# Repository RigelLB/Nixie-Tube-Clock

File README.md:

# Nixie-Tube-Clock
This project is based on the Easy Nixie modules made by allexoK. The following link is the Hackaday page for it: https://hackaday.io/project/192446-easynixie

The circuit itself is decently simple, the version built in the photos doesn't include the capacitors but has issues with some power supplies as the lights' striking wattage (turn on wattage) is quite above the specified 10-watt power supply. The chip used for the logic is just a generic esp32. A wire connects P27 to a plate of brass on the top of the clock. As you touch the plate it will turn on for 5 seconds (specified in code).

As a fair warning, the side usb port was put there to program the esp32 without having to take it in and out of its header pins too many times; however, if the switch isn't flipped to the correct side, no power will be supplied. An alternative is to set up the esp32 to be writable OTA.

Some improvements could be made to the electrical design. If you don't prefer having an both LED's be addressible, the posts that hold up the LED's could be used as the conductor to the second plane. 

The later goal in to add OTA code uploading to the esp32, and add a setup page (via webpage) that modifies the wifi SSID and password, time zone, turn on duration, and other features. Another thing will be to move the code to freeRTOS.

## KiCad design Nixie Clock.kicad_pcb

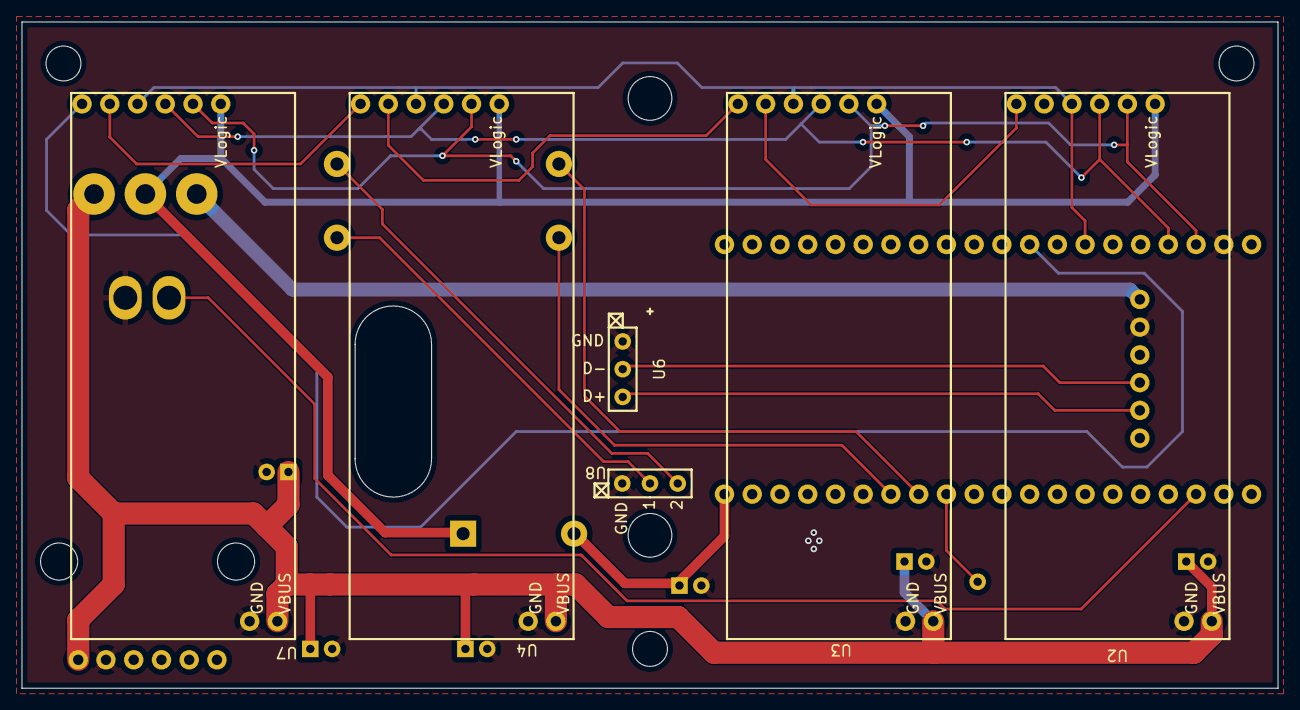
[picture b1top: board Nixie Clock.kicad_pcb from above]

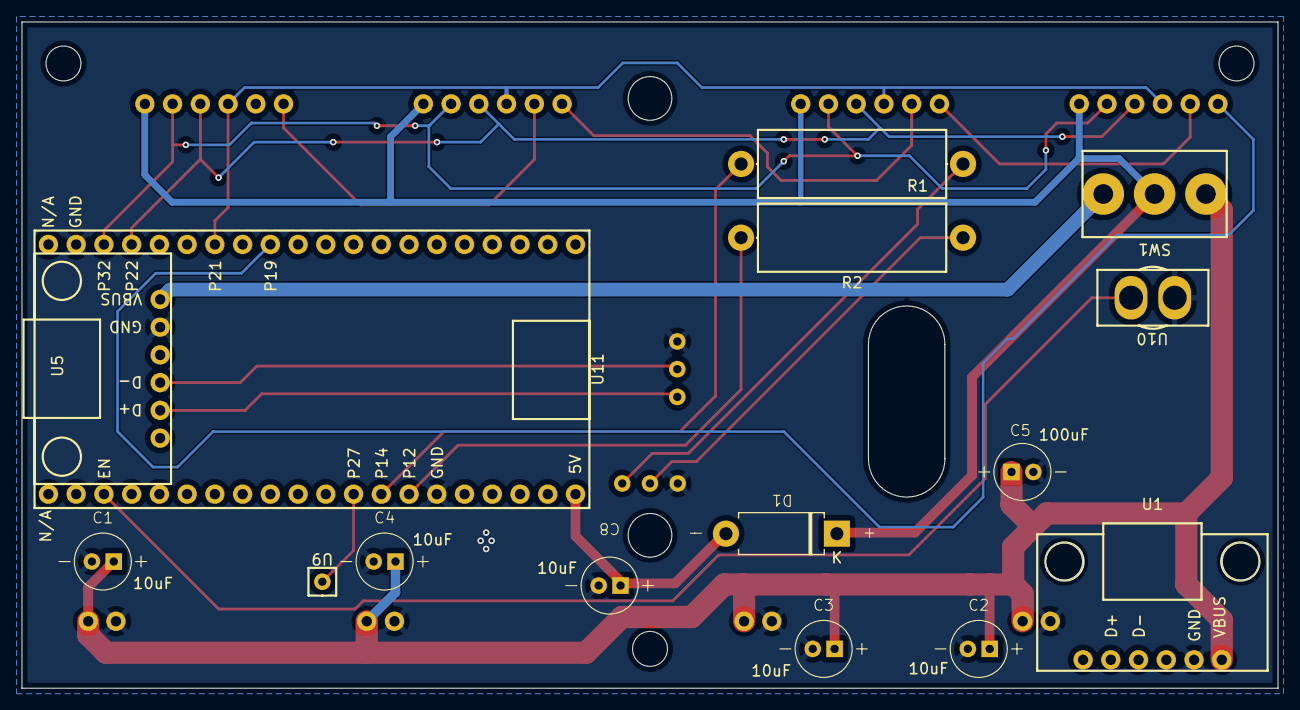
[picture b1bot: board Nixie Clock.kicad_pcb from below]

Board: 2 copper layers, 115.0 x 61.0 mm, 21 parts (15 on the bottom side), 20 nets.

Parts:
C1, C2, C3, C4, C8: 10uF; 100uF Capacitor
C5: 100uF; 100uF Capacitor
D1: D; Diode
R1, R2: 220; R_Axial_DIN0617_L17.0mm_D6.0mm_P20.32mm_Horizontal
SW1: SPDT Switch; ModeSwitch(41-263-0)
U1: Power Only; USBPowerPort
U2: Nixie Driver 4; NixieTubeDriver
U3: Nixie Driver 3; NixieTubeDriver
U4: Nixie Driver 2; NixieTubeDriver
U5: Data Connection; USBPowerPort
U6: 3pin Throughole; 3-Hole Throughole
U7: Nixie Driver 1; NixieTubeDriver
U8: LED Passthrough IN; LED passthrough
U9: Touch Pin; Single Pad
U10: Reset Button; SPST PushButton (SW-PB9-BB00BQE-5)
U11: ESP32 Socket; ESP32 - 40 pin socket

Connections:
GND: C1.2, C2.2, C3.2, C4.2, C5.2, C8.2, U1.2 (GND), U2.8 (GND), U3.8 (GND), U4.8 (GND), U5.2 (GND), U6.1 (GND), U7.8 (GND), U8.1 (GND), U10.1 (GND), U11.15 (GND), U11.39 (GND)
unnamed: C8.1, D1.2 (A), U11.20 (5V)
unnamed: C1.1, C2.1, C3.1, C4.1, C5.1, SW1.3 (A), U1.1 (VBUS), U2.7 (VPOWER), U3.7 (VPOWER), U4.7 (VPOWER), U7.7 (VPOWER)
unnamed: SW1.1 (C), U5.1 (VBUS)
unnamed: U2.1 (DSIN), U3.2 (DSOUT)
unnamed: U3.1 (DSIN), U4.2 (DSOUT)
unnamed: U4.1 (DSIN), U7.2 (DSOUT)
unnamed: U5.5 (D+), U6.3 (D+)
unnamed: U5.4 (D-), U6.2 (D-)
unnamed: R1.1, U8.3 (LED1)
unnamed: R2.1, U8.2 (LED2)
unnamed: U10.2 (EN), U11.3 (EN)
unnamed: R2.2, U11.14 (P12)
unnamed: R1.2, U11.13 (P14)
unnamed: U7.1 (DSIN), U11.32 (P19)
unnamed: U2.3 (STCP), U3.3 (STCP), U4.3 (STCP), U7.3 (STCP), U11.34 (P21)
unnamed: U2.4 (SHCP), U3.4 (SHCP), U4.4 (SHCP), U7.4 (SHCP), U11.37 (P22)
unnamed: U2.5 (OUT_EN), U3.5 (OUT_EN), U4.5 (OUT_EN), U7.5 (OUT_EN), U11.38 (P23)
unnamed: U9.1 (Touch), U11.12 (P27)
VCC: D1.1 (K), SW1.2 (B), U2.6 (VLOGIC), U3.6 (VLOGIC), U4.6 (VLOGIC), U7.6 (VLOGIC)

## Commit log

2025-05-13 Create LICENSE
